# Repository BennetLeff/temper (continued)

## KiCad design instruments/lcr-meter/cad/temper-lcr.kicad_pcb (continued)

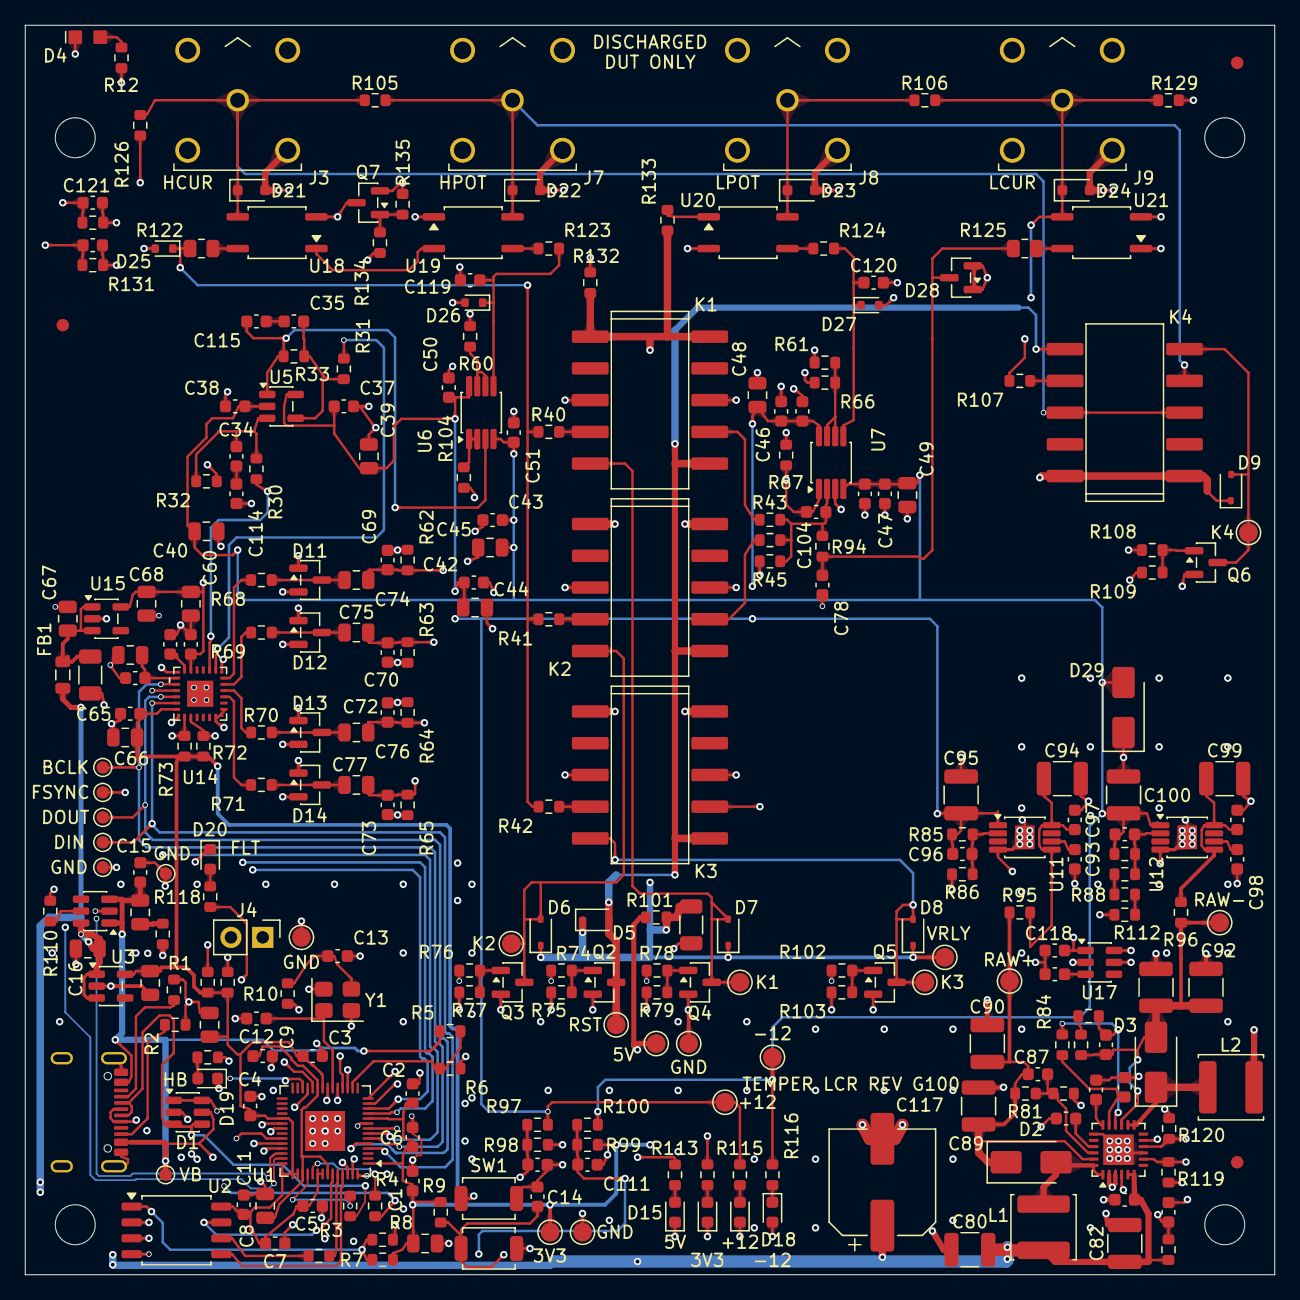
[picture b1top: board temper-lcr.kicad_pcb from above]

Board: 4 copper layers, 100.0 x 100.0 mm, 282 parts (0 on the bottom side), 143 nets.

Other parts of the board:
FID1, FID2, FID3: Fiducial_1mm_Mask2mm
H1, H2, H3, H4: MountingHole_3.2mm_M3
TP1: 5V; TestPoint_Pad_D1.5mm
TP2, TP9, TP22: GND; TestPoint_Pad_D1.5mm
TP3: +12; TestPoint_Pad_D1.5mm
TP4: -12; TestPoint_Pad_D1.5mm
TP5: VRLY; TestPoint_Pad_D1.5mm
TP6: RAW+; TestPoint_Pad_D1.5mm
TP7: RAW-; TestPoint_Pad_D1.5mm
TP8: 3V3; TestPoint_Pad_D1.5mm
TP10: K1; TestPoint_Pad_D1.5mm
TP11: K2; TestPoint_Pad_D1.5mm
TP12: K3; TestPoint_Pad_D1.5mm
TP13: K4; TestPoint_Pad_D1.5mm
TP14: RST; TestPoint_Pad_D1.5mm
TP15: BCLK; TestPoint_Pad_D1.0mm
TP16: FSYNC; TestPoint_Pad_D1.0mm
TP17: DOUT; TestPoint_Pad_D1.0mm
TP18: DIN; TestPoint_Pad_D1.0mm
TP19, TP21: GND; TestPoint_Pad_D1.0mm
TP20: VB; TestPoint_Pad_D1.0mm

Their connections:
3V3: TP8.1; also elsewhere on the board
5V: TP1.1; also elsewhere on the board
12V: TP3.1; also elsewhere on the board
-12V: TP4.1; also elsewhere on the board
GND: TP2.1, TP9.1, TP19.1, TP21.1, TP22.1; also elsewhere on the board
I2S_BCLK: TP15.1; also elsewhere on the board
I2S_DIN: TP18.1; also elsewhere on the board
I2S_DOUT: TP17.1; also elsewhere on the board
I2S_FSYNC: TP16.1; also elsewhere on the board
RAW_N: TP7.1; also elsewhere on the board
RAW_P: TP6.1; also elsewhere on the board
RLY_RST: TP14.1; also elsewhere on the board
RLY_SET_HI: TP12.1; also elsewhere on the board
RLY_SET_LO: TP10.1; also elsewhere on the board
RLY_SET_MED: TP11.1; also elsewhere on the board
RLY_SET_REF: TP13.1; also elsewhere on the board
USB_VBUS: TP20.1; also elsewhere on the board
VRLY: TP5.1; also elsewhere on the board

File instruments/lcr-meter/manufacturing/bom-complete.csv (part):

Designators,Quantity,Value,Manufacturer,MPN,LCSC,Footprint,Assembly,Catalog unit USD,Catalog subtotal USD
"C86,C93,C96,C98,C101,C50,C51,C52,C53",9,10nF 50V,FH (Guangdong Fenghua Advanced Tech),0603B103K500NT,C57112,Capacitor_SMD:C_0603_1608Metric,SMT,0.0101,0.0909
C85,1,4.7nF 50V,FH (Guangdong Fenghua Advanced Tech),0603B472K500NT,C53987,Capacitor_SMD:C_0603_1608Metric,SMT,0.0058,0.0058
C88,1,4.7pF C0G,FH (Guangdong Fenghua Advanced Tech),0603CG4R7C500NT,C1669,Capacitor_SMD:C_0603_1608Metric,SMT,0.0054,0.0054
"R80,R76,R78,R102,R74,R108",6,100R,UNI-ROYAL(Uniroyal Elec),0603WAF1000T5E,C22775,Resistor_SMD:R_0603_1608Metric,SMT,0.0026,0.0156
"R8,R10,R105,R106",4,1k,UNI-ROYAL(Uniroyal Elec),0603WAF1001T5E,C21190,Resistor_SMD:R_0603_1608Metric,SMT,0.003,0.012
"R7,R9,R98,R99",4,10k,UNI-ROYAL(Uniroyal Elec),0603WAF1002T5E,C25804,Resistor_SMD:R_0603_1608Metric,SMT,0.0054,0.0216
"R5,R6,R97,R77,R79,R103,R75,R109,R119,R120",10,100k,UNI-ROYAL(Uniroyal Elec),0603WAF1003T5E,C25803,Resistor_SMD:R_0603_1608Metric,SMT,0.0031,0.031
"R95,R96,R101",3,1R,UNI-ROYAL(Uniroyal Elec),0603WAF100KT5E,C22936,Resistor_SMD:R_0603_1608Metric,SMT,0.0024,0.0072
"R84,R100",2,150k,UNI-ROYAL(Uniroyal Elec),0603WAF1503T5E,C22807,Resistor_SMD:R_0603_1608Metric,SMT,0.0017,0.0034
R111,1,1.5M,UNI-ROYAL(Uniroyal Elec),0603WAF1504T5E,C4172,Resistor_SMD:R_0603_1608Metric,SMT,0.0019,0.0019
R121,1,1.5R,UNI-ROYAL(Uniroyal Elec),0603WAF150KT5E,C22769,Resistor_SMD:R_0603_1608Metric,SMT,0.0028,0.0028
"R110,R115,R116",3,24k 1%,UNI-ROYAL(Uniroyal Elec),0603WAF2402T5E,C23352,Resistor_SMD:R_0603_1608Metric,SMT,0.0024,0.0072
R83,1,240k,UNI-ROYAL(Uniroyal Elec),0603WAF2403T5E,C4197,Resistor_SMD:R_0603_1608Metric,SMT,0.0018,0.0018
"R3,R4",2,27R,UNI-ROYAL(Uniroyal Elec),0603WAF270JT5E,C25190,Resistor_SMD:R_0603_1608Metric,SMT,0.0018,0.0036
"R114,R117,R118",3,3k,UNI-ROYAL(Uniroyal Elec),0603WAF3001T5E,C4211,Resistor_SMD:R_0603_1608Metric,SMT,0.0024,0.0072
R13,1,33R,UNI-ROYAL(Uniroyal Elec),0603WAF330JT5E,C23140,Resistor_SMD:R_0603_1608Metric,SMT,0.0024,0.0024
R12,1,390,UNI-ROYAL(Uniroyal Elec),0603WAF3900T5E,C23151,Resistor_SMD:R_0603_1608Metric,SMT,0.0017,0.0017
R82,1,40.2k,UNI-ROYAL(Uniroyal Elec),0603WAF4022T5E,C12447,Resistor_SMD:R_0603_1608Metric,SMT,0.0021,0.0021
R81,1,430k,UNI-ROYAL(Uniroyal Elec),0603WAF4303T5E,C25969,Resistor_SMD:R_0603_1608Metric,SMT,0.0031,0.0031
"R68,R69,R70,R71",4,470R,UNI-ROYAL(Uniroyal Elec),0603WAF4700T5E,C23179,Resistor_SMD:R_0603_1608Metric,SMT,0.002,0.008
"R72,R73",2,4.7k,UNI-ROYAL(Uniroyal Elec),0603WAF4701T5E,C23162,Resistor_SMD:R_0603_1608Metric,SMT,0.002,0.004
R104,1,47R,UNI-ROYAL(Uniroyal Elec),0603WAF470JT5E,C23182,Resistor_SMD:R_0603_1608Metric,SMT,0.002,0.002
"R1,R2,R113",3,5.1k,UNI-ROYAL(Uniroyal Elec),0603WAF5101T5E,C23186,Resistor_SMD:R_0603_1608Metric,SMT,0.0015,0.0045
R85,1,82k,UNI-ROYAL(Uniroyal Elec),0603WAF8202T5E,C23254,Resistor_SMD:R_0603_1608Metric,SMT,0.0027,0.0027
R86,1,9.1k,UNI-ROYAL(Uniroyal Elec),0603WAF9101T5E,C23260,Resistor_SMD:R_0603_1608Metric,SMT,0.0031,0.0031
"D6,D7,D8,D5,D9",5,1N4148WS,"Jiangsu Changjing Electronics Technology Co., Ltd.",1N4148WS,C2128,Diode_SMD:D_SOD-323,SMT,0.0143,0.0715
Y1,1,12MHz CL10pF,Abracon LLC,ABM8-272-T3,C20625731,Crystal:Crystal_SMD_3225-4Pin_3.2x2.5mm,SMT,0.6471,0.6471
"Q3,Q4,Q5,Q2,Q6",5,AO3400A,Alpha & Omega Semicon,AO3400A,C20917,Package_TO_SOT_SMD:SOT-23,SMT,0.0973,0.4865
"U3,U15",2,3.3V AP2112K,Diodes Incorporated,AP2112K-3.3TRG1,C51118,Package_TO_SOT_SMD:SOT-23-5,SMT,0.1772,0.3544
"R33,R32",2,2k 0.1%,Viking Tech,AR03BTCX2001,C318130,Resistor_SMD:R_0603_1608Metric,SMT,0.0364,0.0728
"R41,R44,R89,R112",4,5k 0.1%,Viking Tech,AR03BTCX5001,C2828621,Resistor_SMD:R_0603_1608Metric,SMT,0.0318,0.1272
"D11,D12,D13,D14",4,BAT54S,hongjiacheng,BAT54S,C7420333,Package_TO_SOT_SMD:SOT-23,SMT,0.0129,0.0516
"J3,J7,J8,J9",4,BNC HCUR,SAMZO,BNC-KYWE-295-W4-N,C41416668,LCR:BNC_SAMZO_KYWE-295-W4-N_Horizontal,Hand fit,1.29,5.16
"C34,C114,C35,C115,C69,C70,C72,C73",8,560pF C0G 5%,YAGEO,CC0603JRNPO9BN561,C107054,Capacitor_SMD:C_0603_1608Metric,SMT,0.0066,0.0528
"C1,C2,C3,C4,C6,C7,C9,C11,C14,C15,C37,C38,C42,C43,C46,C47,C81,C83,C97,C102,C110,C111,C61,C63,C65,C116,C118",27,100nF 50V,YAGEO,CC0603KRX7R9BB104,C14663,Capacitor_SMD:C_0603_1608Metric,SMT,0.0084,0.2268
C5,1,1uF 50V X5R,Samsung Electro-Mechanics,CL10A105KB8NNNC,C15849,Capacitor_SMD:C_0603_1608Metric,SMT,0.0153,0.0153
C62,1,2.2uF 16V X5R,Samsung Electro-Mechanics,CL10A225KO8NNNC,C23630,Capacitor_SMD:C_0603_1608Metric,SMT,0.0119,0.0119
C84,1,220nF 25V,Samsung Electro-Mechanics,CL10B224KA8NNNC,C21120,Capacitor_SMD:C_0603_1608Metric,SMT,0.0097,0.0097
"C104,C78",2,100pF C0G 5%,Samsung Electro-Mechanics,CL10C101JB8NNNC,C14858,Capacitor_SMD:C_0603_1608Metric,SMT,0.0086,0.0172
"C12,C13,C87",3,15pF C0G,Samsung Electro-Mechanics,CL10C150JB8NNNC,C1644,Capacitor_SMD:C_0603_1608Metric,SMT,0.0111,0.0333
"C18,C60,C64,C66",4,10uF 25V X5R,Samsung Electro-Mechanics,CL21A106KAYNNNE,C15850,Capacitor_SMD:C_0805_2012Metric,SMT,0.0773,0.3092
C113,1,4.7uF 25V X5R,Samsung Electro-Mechanics,CL21A475KAQNNNE,C1779,Capacitor_SMD:C_0805_2012Metric,SMT,0.0343,0.0343
"C8,C10,C16,C17,C39,C40,C44,C45,C48,C49,C67,C68,C74,C75,C76,C77",16,1uF 50V,Samsung Electro-Mechanics,CL21B105KBFNNNE,C28323,Capacitor_SMD:C_0805_2012Metric,SMT,0.0344,0.5504
"C103,C112",2,22uF 25V X5R,Samsung Electro-Mechanics,CL31A226KAHNNNE,C12891,Capacitor_SMD:C_1206_3216Metric,SMT,0.1798,0.3596
"C80,C82,C89,C90,C91,C92,C94,C95,C99,C100",10,10uF 50V X7R,Samsung Electro-Mechanics,CL32B106KBJNNNE,C138687,Capacitor_SMD:C_1210_3225Metric,SMT,0.33,3.3
"L1,L2",2,4.7uH 3.8A shielded,cjiang (Changjiang Microelectronics Tech),FNR5040S4R7MT,C167963,Inductor_SMD:L_Changjiang_FNR5040S,SMT,0.0621,0.1242
U2,1,GD25Q16ESIGR,GigaDevice,GD25Q16ESIGR,C2922792,Package_SO:SOIC-8_5.3x5.3mm_P1.27mm,SMT,0.6011,0.6011
FB1,1,100R@100MHz 800mA,Sunlord,GZ2012D101TF,C1015,Inductor_SMD:L_0805_2012Metric,SMT,0.0311,0.0311
"D15,D16,D17,D18,D19,D20",6,RED,Hubei KENTO Elec,KT-0603R,C2286,LED_SMD:LED_0603_1608Metric,SMT,0.0073,0.0438
U17,1,LM3880-1AA,Texas Instruments,LM3880MF-1AA/NOPB,C486059,Package_TO_SOT_SMD:SOT-23-6,SMT,1.8617,1.8617
D4,1,ORANGE,Lite-On,LTST-S270KFKT,C160472,LCR:LED_LiteOn_LTST-S270KFKT_SideView,SMT,0.0382,0.0382
U5,1,OPA197IDBVR,Texas Instruments,OPA197IDBVR,C221351,Package_TO_SOT_SMD:SOT-23-5,SMT,0.5978,0.5978
"U6,U7",2,OPA2810IDGKR,Texas Instruments,OPA2810IDGKR,C2864204,Package_SO:VSSOP-8_3x3mm_P0.65mm,SMT,5.09,10.18
C117,1,330uF 10V polymer,Nichicon,PCG1A331MCL1GS,C433208,Capacitor_SMD:CP_Elec_8x6.9,SMT,1.1292,1.1292
U1,1,RP2040,Raspberry Pi,RP2040,C2040,Package_DFN_QFN:QFN-56-1EP_7x7mm_P0.4mm_EP3.2x3.2mm,SMT,1.0752,1.0752
"R42,R45,R87",3,100k 0.1%,YAGEO,RT0603BRD07100KL,C122538,Resistor_SMD:R_0603_1608Metric,SMT,0.0322,0.0966
"R40,R43",2,100R 0.1%,YAGEO,RT0603BRD07100RL,C122970,Resistor_SMD:R_0603_1608Metric,SMT,0.0319,0.0638
"R88,R60,R61,R66,R67,R62,R63,R64,R65,R107",10,1k 0.1%,YAGEO,RT0603BRD071KL,C110776,Resistor_SMD:R_0603_1608Metric,SMT,0.0313,0.313
R94,1,22R 0.1%,YAGEO,RT0603BRD0722RL,C861239,Resistor_SMD:R_0603_1608Metric,SMT,0.0318,0.0318
"R31,R30",2,2.2k 0.1%,YAGEO,RT0603BRD072K2L,C861295,Resistor_SMD:R_0603_1608Metric,SMT,0.0363,0.0726
D1,1,SRV05-4,hongjiacheng,SRV05-4,C7420376,Package_TO_SOT_SMD:SOT-23-6,SMT,0.0851,0.0851
"D2,D3",2,SS14,MDD(Microdiode Semiconductor),SS14,C2480,Diode_SMD:D_SMA,SMT,0.0192,0.0384
U14,1,TAC5112,Texas Instruments,TAC5112IRGER,C44853692,LCR:TI_RGE0024R_VQFN-24-1EP_4x4mm_P0.5mm_EP2.1mm_CornerPads,SMT,5.93,5.93
U16,1,TPS2553,Texas Instruments,TPS2553DBVR,C55266,Package_TO_SOT_SMD:SOT-23-6,SMT,0.5412,0.5412
U13,1,TPS65131RGER,Texas Instruments,TPS65131RGER,C87663,Package_DFN_QFN:VQFN-24-1EP_4x4mm_P0.5mm_EP2.45x2.45mm,SMT,2.8743,2.8743
U12,1,TPS7A3001DGNR,Texas Instruments,TPS7A3001DGNR,C33835,Package_SO:HVSSOP-8-1EP_3x3mm_P0.65mm_EP1.57x1.89mm,SMT,2.0197,2.0197
U11,1,TPS7A4901DGNR,Texas Instruments,TPS7A4901DGNR,C16430,Package_SO:HVSSOP-8-1EP_3x3mm_P0.65mm_EP1.57x1.89mm,SMT,1.4494,1.4494
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
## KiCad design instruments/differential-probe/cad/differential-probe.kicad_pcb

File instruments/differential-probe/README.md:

# Temper differential probe — Rev C PCB prototype

Three-sheet KiCad design and fully routed four-layer PCB for measuring the stage-53 coil and resonant capacitor bank. Rev C is a compacted, simplified Rev B with every function kept. It is an engineering prototype; voltage, stability and CMRR targets still require qualification of the assembled probe in its enclosure.

**Start here:** [Rev C design record](docs/revc.md) — reasoning, calculations, rejected options and the before/after table against Rev B.

- [Schematic PDF](previews/differential-probe.pdf)
- [KiCad project](cad/differential-probe.kicad_pro) and [root schematic](cad/differential-probe.kicad_sch)
- [Routed PCB](cad/differential-probe.kicad_pcb), [3D preview](previews/pcb-3d.png), and [copper / assembly layers PDF](previews/pcb-layers.pdf)
- [Layout, enclosure and mounting requirements](docs/layout.md)
- [BOM exported from the schematic](bom.csv), with exact manufacturer part numbers, footprints and datasheet links
- [Circuit decisions and assembly notes](docs/design.md)
- [Calibration and qualification plan](docs/qualification.md)
- [Electrical checks](validation/checks.txt), [ERC report](validation/erc.rpt), and [package/pad audit](validation/footprint-audit.tsv)
- [PCB connectivity and symmetry checks](validation/pcb-checks.txt), [native DRC](validation/pcb-drc.json), and [spacing-rule negative controls](validation/pcb-drc-oracle.txt)
- [OPA2810/OPA810 vendor-model checks](validation/spice/results.txt)
- [Procurement package](procurement/README.md) (draft; nothing ordered)

The board is 150 × 70 mm, four layers, and carries every component.

- **HV dividers.** The two dividers are mirror images about an open-ended inter-leg notch, at a 23 mm leg pitch. Each leg has five 2 MΩ / 33 pF sections.
- **Spacing.** There are ten routed capacitor slots and no planes under the HV ladders.
- **Panel parts.** The output BNC, the overvoltage-trigger BNC, the range switch and the power switch are PCB-mounted at the output edge. The two 9 V holders sit on the underside of the low-voltage section.

Native KiCad DRC reports zero violations and zero unconnected items with the explicit HV rules and `--all-track-errors`. These checks establish geometry and connectivity, not a qualified 3 kV or CAT rating.

## Specification carried into this design

| Item | Design target / implementation |
|---|---|
| Input divider | Two fixed 2000:1 dividers; five compensated sections per leg |
| Each upper section | One 2 MΩ, 1%, 3 kV HV12 2512 resistor, shunted by 33 pF NP0 / 3 kV ([cost-down](docs/cost-down.md)) |
| Low leg | 4.87 kΩ, 0.1% plus 500 Ω trim; 10 nF fixed + two select-on-test C0G + 12–60 pF top-adjust trimmer |
| Amplifiers | OPA2810 dual buffer; OPA2810 ×2 subtractor + coax driver; OPA810 ×5 stage |
| Output gain | Fixed ×2 subtractor and fixed ×5 stage; output selection gives nominal 1000:1 / 200:1 ratios |
| Initial differential range target | ±1.5 kV at 1000:1; ±300 V at 200:1 |
| Extended range to qualify | ±3 kV at 1000:1; ±600 V at 200:1 |
| Initial tip-to-earth target | Each tip within ±1.5 kV; extend separately to ±3 kV |
| Bandwidth | DC–5 MHz small-signal target; vendor-model −3 dB 5.77 MHz wide / 5.27 MHz fine (two-pole output filter; cutting JP1 gives 10.9 / 8.4 MHz) |
| Output noise (vendor model, tip-referred) | 172 mV rms wide / 116 mV fine over 10 Hz–200 MHz; 127 / 109 mV to 20 MHz; 72 / 71 mV to 5 MHz ([output-filter study](validation/spice/output-filter-study.txt)); not yet measured ([qualification §3](docs/qualification.md#3-ac-compensation-and-frequency-response)) |
| Initial-envelope warning | Nominal 1.363 kV per tip; 1.239 kV wide / 248 V fine differential, latched |
| Main measurement band | 35–60 kHz; proposed acceptance ±2% amplitude, ≤1° phase after calibration |
| Common-mode rejection | 60 dB goal; measure versus frequency and apply a measurement-specific error budget. Worst-case C0G drift alone gives 58.4 dB after a 10 °C change, so calibrate pair-matched on the CM jig at the operating temperature, with same-reel divider capacitors ([qualification §4](docs/qualification.md#cmrr-calibration-procedure)) |
| Input loading | Ideal 10.005 MΩ and about 6.6 pF per tip; with leads and enclosure 11.7–11.9 pF per tip (option-B estimates, target ≤ 12 pF; [HV leads](docs/hv-leads.md#capacitance-budget)) |
| Scope | 1 MΩ input, short BNC cable; do not select 50 Ω termination |
| Power | Two 9 V batteries, regulated to approximately +4.80 / −4.81 V |
| Enclosure | Owner-designed earthed shield (Hammond 1455N2201 is the reference geometry); 20 mm HV-to-metal setback in 3-D and the other requirements in the [Rev C record](docs/revc.md#9-size-layers-enclosure) |

All voltage ratings and performance limits above are **qualification targets**. Full voltage at 5 MHz is not implied. Input-to-earth voltage, differential voltage, frequency, temperature and duration must all stay inside the eventual measured envelope.

The compact spacing design requires all three extended limits at once: `|V+| ≤ 3 kV`, `|V−| ≤ 3 kV` and `|V+ − V−| ≤ 3 kV`. It does not claim survival with opposing +3 kV / −3 kV tips. A differential input can exceed its range even when each tip is within its earth-voltage limit.

## Main selected parts

| Function | Selected MPN | Quantity |
|---|---|---:|
| Upper divider resistors | Uni-Royal HV121WF2004T4E (2 MΩ, 1%, 1 W, 3 kV) | 10 |
| Upper compensation | Yageo CC1812JKNPOEBN330, 33 pF NP0, 3 kV | 10 |
| Low-leg fixed resistors (also the rails-OK ladders and R126) | Yageo RT0603BRD074K87L (4.87 kΩ, 0.1%) | 2 + 5 |
| Gain-setting precision resistors | Stackpole RNCF0603TKY499R / 1K00 / 2K00 | 3 / 2 / 1 |
| Low-leg capacitors | Yageo CC1206FKNPO9BN103 + select-on-test C0805C302F5GACTU / C0805C161F5GACTU | 2 + 2 + 2 |
| DC trim | Bourns 3296W-1-501LF (500 Ω) | 2 |
| Analog zero trims, one per range | Bourns 3296W-1-203LF (20 kΩ) | 2 |
| AC compensation trim | EW Electronics GKG60015, 12–60 pF | 2 |
| Buffers, subtractor, driver | TI OPA2810IDR | 2 |
| ×5 stage | TI OPA810IDR | 1 |
| Low-leakage clamps | Nexperia BAV199,215 | 4 |
| Overload comparators | TI TLV1704AIPWR / TLV1702AIDGKR | 1 each |
| Overload latch (flip-flop 2 drives the trigger output) | TI CD4013BM96 | 1 |
| Regulators | ADP7142AUJZ-R7 / ADP7182AUJZ-R7 | 1 each |
| Range / power switches (PCB) | E-Switch 100SP1T1B5M7RE / 100DP1T1B1M7QEH | 1 each |
| Rails-OK window references / indicator LED | JSCJ CJ431 / Hubei KENTO KT-0805G (green) | 4 / 1 |
| BNC (PCB, bulkhead): output J3, trigger J4 | Amphenol RF 031-5431-10RFX | 2 |
| 9 V holders (PCB, underside) | MPD BH9VPC | 2 |

The BOM contains every component.

- **Cost-down (2026-10-20).** The divider uses 1% HV12 bodies stocked at JLC instead of the 0.1% HVCB2512 (9 at DigiKey, 0 at LCSC). The 4.87 kΩ + 500 Ω trim covers both a 1% and a 0.1% string, so Stackpole HVCB2512BDE2M00 remains a drop-in upgrade. The margin costs (DC CMRR drift with temperature, one fault case at the ±3 kV extension) are quantified in [cost-down](docs/cost-down.md).
- **HV leads (option B).** Two dedicated probes, docked permanently on stage 53: probe 1 on the bank (TIP+ ring on J5, TIP− soldered into C22's free hole), probe 2 on the coil (rings on J5 and J2). The captive silicone leads (generic wire accepted by incoming hipot; UL 3239 10 kV DC fallbacks) leave through nylon glands in a printed wall insert and run in printed spines and docks generated in CadQuery ([`mech3d/`](mech3d/README.md)). Routing, stud stacks, loading budget and assembly are in [HV leads](docs/hv-leads.md). Ordinary SMA, 1 kV test leads or low-voltage terminal blocks are not acceptable for the HV inputs.

## Stage-53 identity

This work uses the user-selected stage 53, not the older stage15b baseline in the repository's general instructions.

Board: `worktrees/runs-native21/s53/c53int/section.kicad_pcb` relative to the repository root.

SHA-256: `82af7bd93e62d1f2e6c7c2c2b971a4830bf6e09078bae3f269d8bead9a31fd27`.

The coil spans `COIL_FEED`–`RES_A`; the capacitor bank spans `RES_A`–`SW_B`. The latter includes a bridge switch node, so probe-to-earth displacement current is a design constraint even when the wanted signal is the 35–60 kHz tank waveform. The bank is five 100 nF capacitors, 0.5 µF total. The inherited stage-53 studies include approximately 566 Vpk design operation, 775 Vpk no-pan, and 1.62–1.79 kV fault cases; these are simulation/design records, not measurements made with this probe.

The [CT correction](docs/stage53-ct-correction.md) verifies T1 as CST3015-200ED with a 3 Ω burden and recalculates its volt-second margin. Historical fixture documents and the stale model reference are addressed in a [scoped maintenance patch](maintenance/README.md).

Source records: `worktrees/ps-integrate/zapote/power-stage-120v/validation-results/11-candidates/c53-cert-provisions/stage53/README.md` and the `validation-results/08-manufacturing-package/native-21/review-packet-s53/` directory in that worktree. The fault envelope is why the 3 kV extension remains useful.

## Reproduce and edit

From this directory, run `make pcb` to regenerate the schematic and PCB, check them, and refresh previews. `make all` retains the schematic-only workflow. Optional `make simulate` verifies the archived model/testbench hashes and reruns the nominal OPA2810/OPA810 checks with ngspice. Requirements are KiCad 10, its native Python/pcbnew module, Rust, jq, and the standard KiCad libraries. The current tools use the macOS KiCad library location; adjust path constants and `KICAD_PYTHON` for another installation.

`tools/build.rs` is the deterministic authoring source for circuit selections, connections and sheet placement. It generates the native KiCad files and intended-pin records. `make export` exports PDF, SVG, XML netlist, BOM and ERC from those native files. `tools/check.rs` compares the exported connectivity against the intended pin groups, checks selected critical package pin mappings and footprint pad sets, and records ideal divider calculations. It does not simulate the ICs or establish high-voltage safety.

Edit the Rust authoring source for reproducible changes. Direct KiCad edits are possible, but a subsequent `make generate` replaces them; reconcile such edits into the authoring source first. Never hand-edit the generated BOM.

`tools/layout.rs` owns placement, hand-authored routing and HV rules; `tools/pcb_bridge.py` only adapts those records to native KiCad geometry and zone filling. `make pcb-generate` overwrites the canonical board, so reconcile manual PCB edits before regenerating. Existing project design settings are preserved. `make pcb-check` audits the current saved board without regenerating it. `make pcb-oracle` proves that a deliberately close grounded track, a removed capacitor slot, a closed inter-leg notch and a shortened notch each fail the relevant native DRC rules. Opposite-tip fixtures pass at 20.5 mm and fail at 8 mm edge spacing under the 10 mm air / 20 mm surface rules. Fixtures stay in ignored `build/`. `sh procurement/export.sh` regenerates the draft fabrication/assembly package.

Rev A is preserved in commit `14eda6c86`. Rev B is preserved unchanged at commit `ca79d882f` on `codex/differential-probe-revb`; its circuit record, build decision and layout handoff remain in `docs/`. Rev C is developed on `claude/differential-probe-revc`.

The original scratchpad analysis is preserved verbatim in `evidence/2026-10-20-divider.py`, with its original output. It is historical ideal-RC analysis, not the authoring source or proof of this complete circuit's performance.

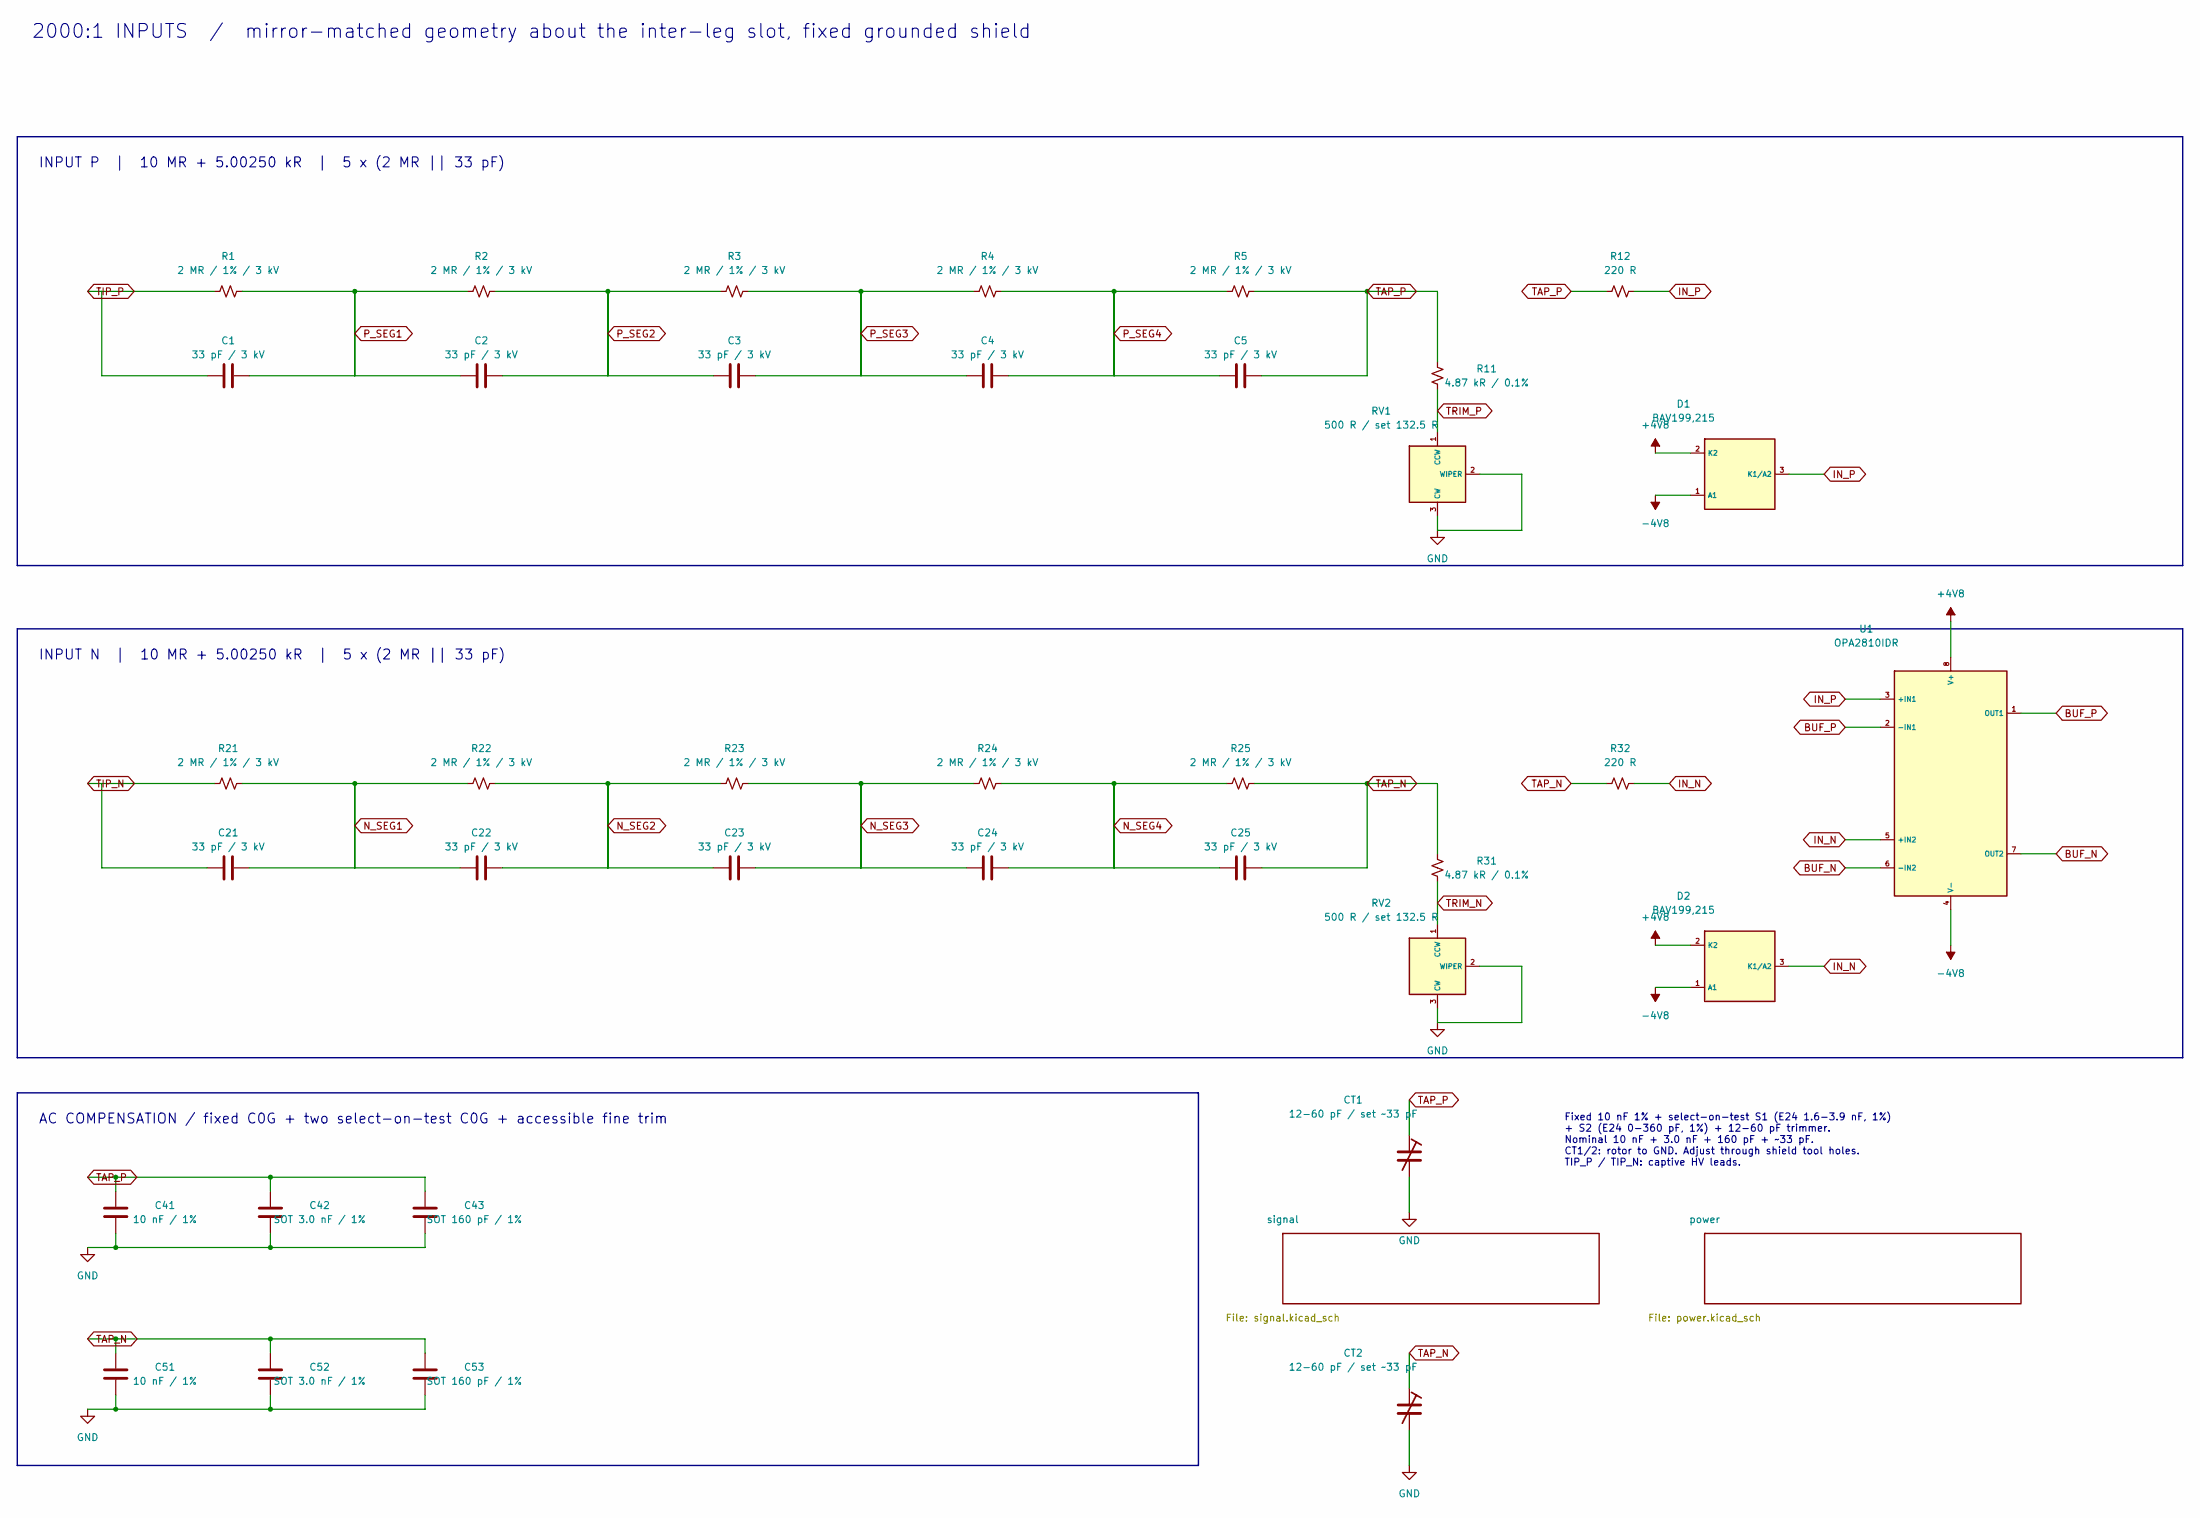
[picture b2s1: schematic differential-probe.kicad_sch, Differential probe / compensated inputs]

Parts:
C1, C2, C3, C4, C5, C21, C22, C23, C24, C25: 33 pF / 3 kV; C_1812_HV_Slot; MPN CC1812JKNPOEBN330; LCSC C2359543
C41, C51: 10 nF / 1%; C_1206_3216Metric; MPN CC1206FKNPO9BN103; LCSC C541597
C42, C52: SOT 3.0 nF / 1%; C_0805_2012Metric; MPN C0805C302F5GACTU
C43, C53: SOT 160 pF / 1%; C_0805_2012Metric; MPN C0805C161F5GACTU
CT1, CT2: 12-60 pF / set ~33 pF; GKG60015_TopAdjust; MPN GKG60015
D1, D2: BAV199,215; SOT-23; MPN BAV199,215; LCSC C40919
R1, R2, R3, R4, R5, R21, R22, R23, R24, R25: 2 MR / 1% / 3 kV; R_2512_6332Metric; MPN HV121WF2004T4E; LCSC C2779442
R11, R31: 4.87 kR / 0.1%; R_0603_1608Metric; MPN RT0603BRD074K87L; LCSC C861446
R12, R32: 220 R; R_0805_2012Metric; MPN 0805W8F2200T5E; LCSC C17557
RV1, RV2: 500 R / set 132.5 R; Potentiometer_Bourns_3296W_Vertical; MPN 3296W-1-501LF; LCSC C69564
U1: OPA2810IDR; SOIC-8_3.9x4.9mm_P1.27mm; MPN OPA2810IDR; LCSC C1849413

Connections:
+4V8: D1.2 (K2), D2.2 (K2), U1.8 (V+); also elsewhere on the board
-4V8: D1.1 (A1), D2.1 (A1), U1.4 (V-); also elsewhere on the board
BUF_N: U1.6 (-IN2), U1.7 (OUT2); also elsewhere on the board
BUF_P: U1.1 (OUT1), U1.2 (-IN1); also elsewhere on the board
GND: C41.2, C42.2, C43.2, C51.2, C52.2, C53.2, CT1.2, CT2.2, RV1.2 (WIPER), RV1.3 (CW), RV2.2 (WIPER), RV2.3 (CW); also elsewhere on the board
IN_N: D2.3 (K1/A2), R32.2, U1.5 (+IN2)
IN_P: D1.3 (K1/A2), R12.2, U1.3 (+IN1)
N_SEG1: C21.2, C22.1, R21.2, R22.1
N_SEG2: C22.2, C23.1, R22.2, R23.1
N_SEG3: C23.2, C24.1, R23.2, R24.1
N_SEG4: C24.2, C25.1, R24.2, R25.1
P_SEG1: C1.2, C2.1, R1.2, R2.1
P_SEG2: C2.2, C3.1, R2.2, R3.1
P_SEG3: C3.2, C4.1, R3.2, R4.1
P_SEG4: C4.2, C5.1, R4.2, R5.1
TAP_N: C25.2, C51.1, C52.1, C53.1, CT2.1, R25.2, R31.1, R32.1
TAP_P: C5.2, C41.1, C42.1, C43.1, CT1.1, R5.2, R11.1, R12.1
TIP_N: C21.1, R21.1; also elsewhere on the board
TIP_P: C1.1, R1.1; also elsewhere on the board
TRIM_N: R31.2, RV2.1 (CCW)
TRIM_P: R11.2, RV1.1 (CCW)

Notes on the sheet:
2000:1 INPUTS / mirror-matched geometry about the inter-leg slot, fixed grounded shield
INPUT P | 10 MR + 5.00250 kR | 5 x (2 MR || 33 pF)
INPUT N | 10 MR + 5.00250 kR | 5 x (2 MR || 33 pF)
AC COMPENSATION / fixed C0G + two select-on-test C0G + accessible fine trim
Fixed 10 nF 1% + select-on-test S1 (E24 1.6-3.9 nF, 1%) + S2 (E24 0-360 pF, 1%) + 12-60 pF trimmer. Nominal 10 nF + 3.0 nF + 160 pF + ~33 pF. CT1/2: rotor to GND. Adjust through shield tool holes. TIP_P / TIP_N: captive HV leads.
